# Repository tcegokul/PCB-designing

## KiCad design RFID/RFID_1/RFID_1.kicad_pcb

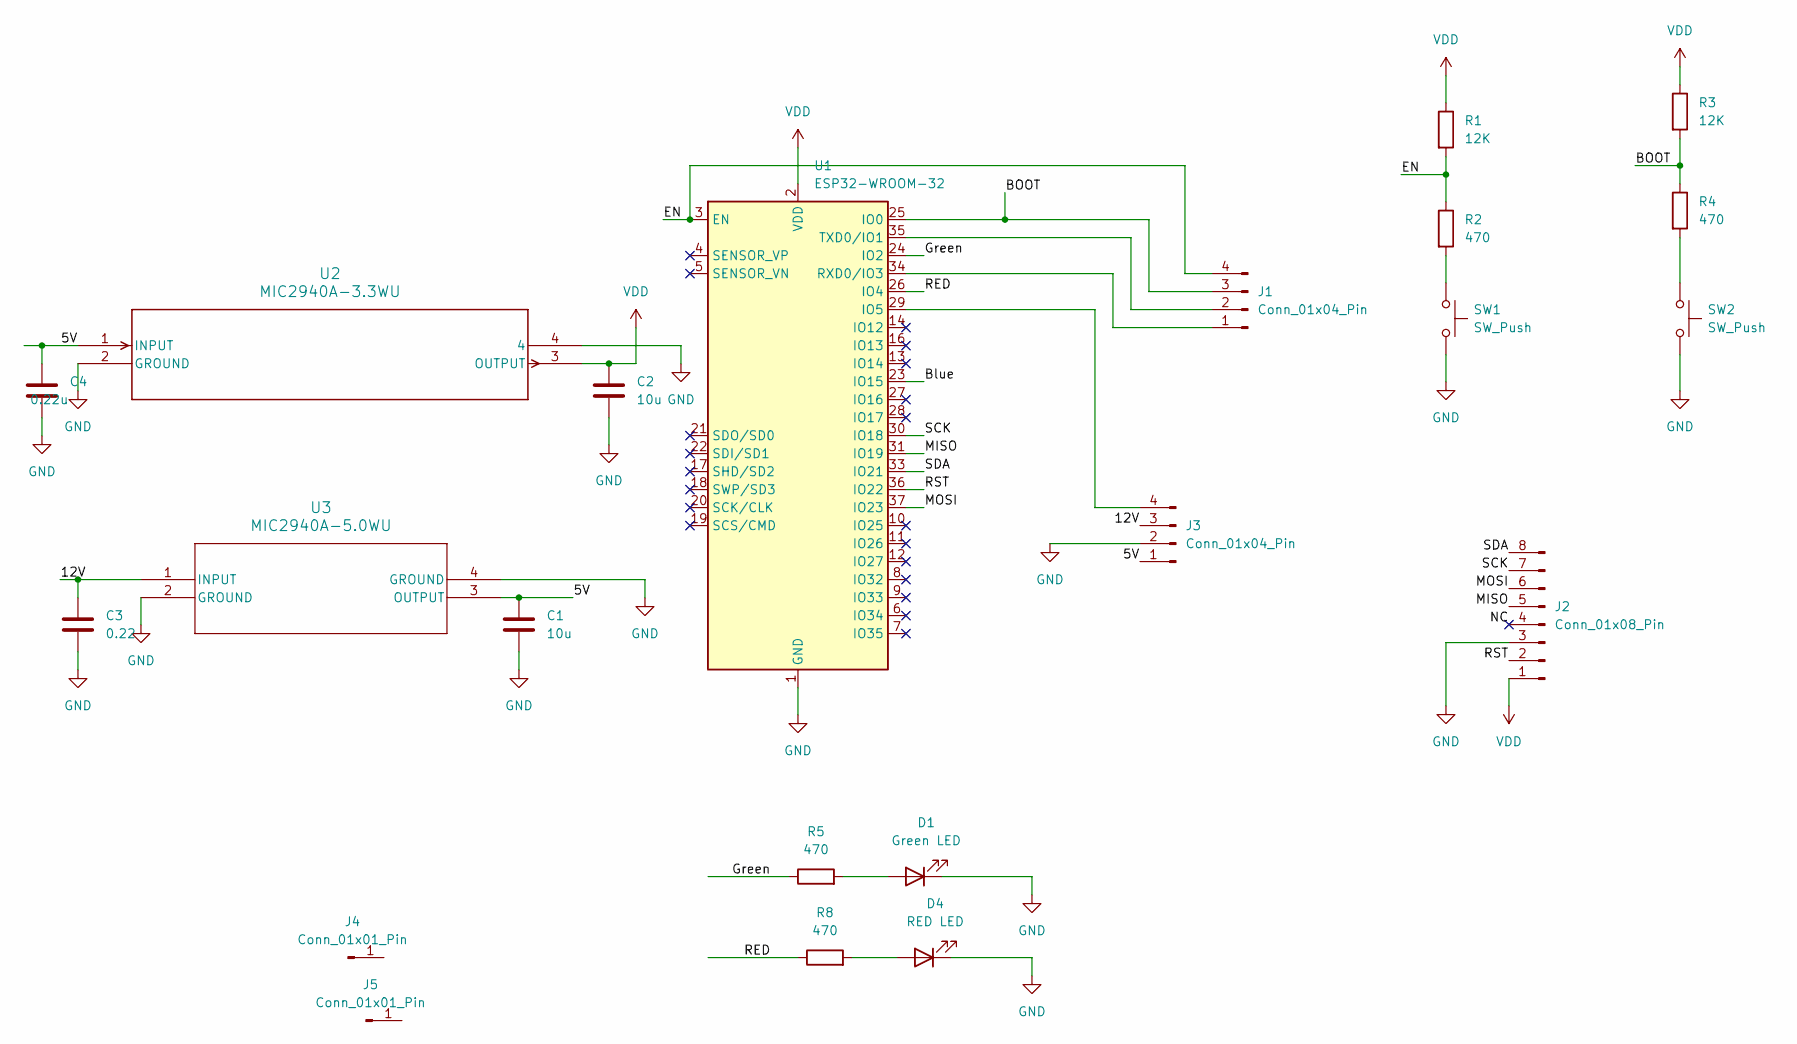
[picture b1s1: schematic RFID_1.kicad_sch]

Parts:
C1, C2: 10u; C_0805_2012Metric_Pad1.18x1.45mm_HandSolder
C3: 0.22; C_0805_2012Metric_Pad1.18x1.45mm_HandSolder
C4: 0.22u; C_0805_2012Metric_Pad1.18x1.45mm_HandSolder
D1: Green LED; LED_0805_2012Metric_Pad1.15x1.40mm_HandSolder
D4: RED LED; LED_0805_2012Metric_Pad1.15x1.40mm_HandSolder
J1: Conn_01x04_Pin; PinHeader_1x04_P2.54mm_Vertical
J2: Conn_01x08_Pin; PinSocket_1x08_P2.54mm_Vertical
J3: Conn_01x04_Pin; CONN4_500000G_AMP
J4, J5: Conn_01x01_Pin; pad_clearancefu
R1, R3: 12K; R_0805_2012Metric_Pad1.20x1.40mm_HandSolder
R2, R4, R5, R8: 470; R_0805_2012Metric_Pad1.20x1.40mm_HandSolder
SW1, SW2: SW_Push; SW_Push_1P1T_NO_6x6mm_H9.5mm
U1: ESP32-WROOM-32
U2: MIC2940A-3.3WU; TO263-3LD_MCH
U3: MIC2940A-5.0WU; TO263-3LD_MCH

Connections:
/5V: C1.1, C4.1, J3.1, U2.1 (INPUT), U3.3 (OUTPUT)
/12V: C3.1, J3.3, U3.1 (INPUT)
/BOOT: J1.3, R3.2, R4.1, U1.25 (IO0)
/Blue: U1.23 (IO15)
/EN: J1.4, R1.2, R2.1, U1.3 (EN)
/Green: R5.1, U1.24 (IO2)
/MISO: J2.5, U1.31 (IO19)
/MOSI: J2.6, U1.37 (IO23)
/NC: J2.4
/RED: R8.1, U1.26 (IO4)
/RST: J2.2, U1.36 (IO22)
/SCK: J2.7, U1.30 (IO18)
/SDA: J2.8, U1.33 (IO21)
GND: C1.2, C2.2, C3.2, C4.2, D1.1 (K), D4.1 (K), J2.3, J3.2, J4.1, J5.1, SW1.2, SW2.2, U1.1 (GND), U1.15 (GND), U1.38 (GND), U1.39 (GND), U2.2 (GROUND), U2.4, U3.2 (GROUND), U3.4 (GROUND)
unnamed: D1.2 (A), R5.2
unnamed: D4.2 (A), R8.2
unnamed: J1.1, U1.34 (RXD0/IO3)
unnamed: J1.2, U1.35 (TXD0/IO1)
unnamed: J3.4, U1.29 (IO5)
unnamed: R2.2, SW1.1
unnamed: R4.2, SW2.1
VDD: C2.1, J2.1, R1.1, R3.1, U1.2 (VDD), U2.3 (OUTPUT)

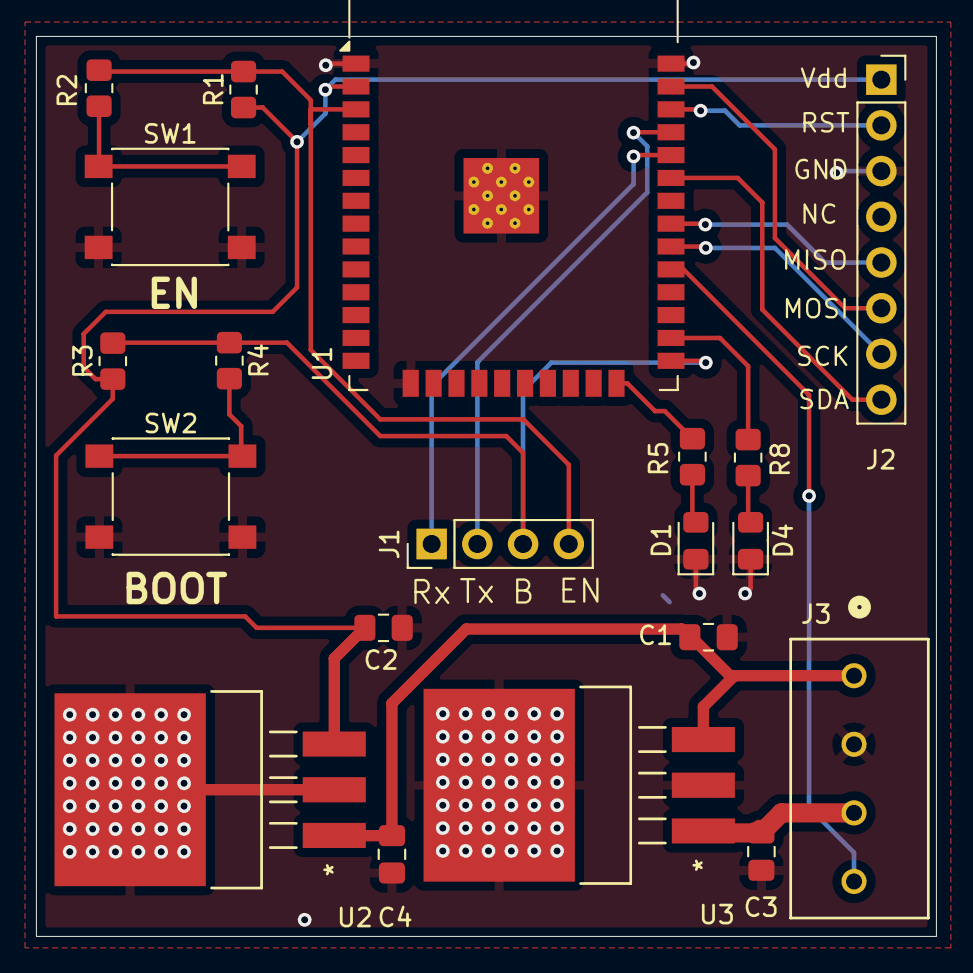
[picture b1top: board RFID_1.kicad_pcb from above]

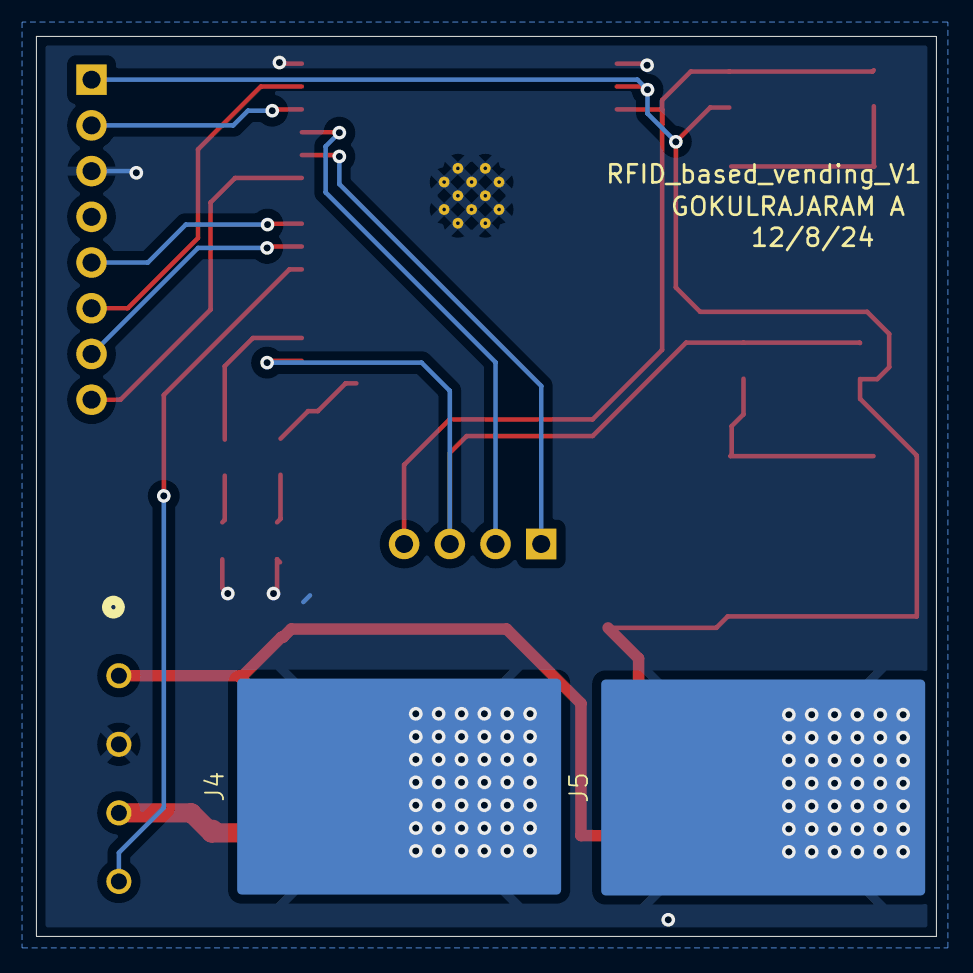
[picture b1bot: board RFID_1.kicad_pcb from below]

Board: 2 copper layers, 50.0 x 50.0 mm, 22 parts (2 on the bottom side), 20 nets.

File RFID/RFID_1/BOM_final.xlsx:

Sr No | Qunatity | Reference | Value | Part type | PCB foot print | Manufacture part number / Generic part number | Manufacturer Name | Description
1 | 2 | C1,C2 | 10uF | CAP | Capacitor_SMD:C_0805_2012Metric_Pad1.18x1.45mm_HandSolder | GPC0805106-16
2 | 1 | C3,C4 | 0.22uF | CAP | Capacitor_SMD:C_0805_2012Metric_Pad1.18x1.45mm_HandSolder | CL21B224KCFSNWE | Samsung Electro-Me chanics
3 | 1 | D1 | Green LED | LED | LED_SMD:LED_0805_2012Metric_Pad1.15x1.40mm_HandSolder | 150080BS75000 | Würth Elektronik | blue lEDs
4 | 1 | D4 | RED LED | LED | LED_SMD:LED_0805_2012Metric_Pad1.15x1.40mm_HandSolder | 150080BS75000 | Würth Elektronik | Blue LEDs
5 | 1 | J1 | Conn_01x04_Pin | male Connector | Connector_PinHeader_2.54mm:PinHeader_1x04_P2.54mm_Vertical | PH1-04-UA
6 | 1 | J3 | Conn_01x04_Pin | wire to board connector | footprints_screw_connector:CONN4_500000G_AMP | YO0421500000G | Amphenol Anytek | 4 Position Wire to Board Terminal Block Horizontal with Board 0.150" (3.81mm) T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
7 | 1 | J2 | Conn_01x08_Pin | Female connector | Connector_PinSocket_2.54mm:PinSocket_1x08_P2.54mm_Vertical | 61300811821
8 | 2 | R1,R3 | 12k | Resistor | Resistor_SMD:R_0805_2012Metric_Pad1.20x1.40mm_HandSolder | RMCF0805JT12K0 | Stackpole Electronics Inc | RES 12K OHM 5% 1/8W 0805
9 | 4 | R2,R4,R5,R8 | 470 | Resistor | Resistor_SMD:R_0805_2012Metric_Pad1.20x1.40mm_HandSolder | GPR0805470R
10 | 1 | U1 | ESP32-Wroom-32 | ESP32-WROOM-32-N4 | RF_Module:ESP32-WROOM-32 | ESP32-WROOM-32E-N4 | Espressif Systems | RF TXRX MOD BT WIFI TH SMD
11 | 1 | U2 | MIC2940A-3.3WU | MIC2940A-3.3WU | footprints:TO263-3LD_MCH | MIC2940A-3.3WU | Microchip Technology | IC REG LINEAR 3.3V 1.25A TO263-3
12 | 1 | U3 | MIC2940A-5.0WU | MIC2940A-5.0WU | footprints_5v:TO263-3LD_MCH | MIC2940A-5.0WU | Microchip Technology | IC REG LINEAR 5V 1.25A TO263-3
13 | 2 | SW1,SW2 | Switch | Switch | Button_Switch_SMD:SW_Push_1P1T_NO_6x6mm_H9.5mm | FSM2JSMAATR | TE Connectivity ALCOSWITCH Switches | SWITCH TACTILE SPST-NO 0.05A 24V

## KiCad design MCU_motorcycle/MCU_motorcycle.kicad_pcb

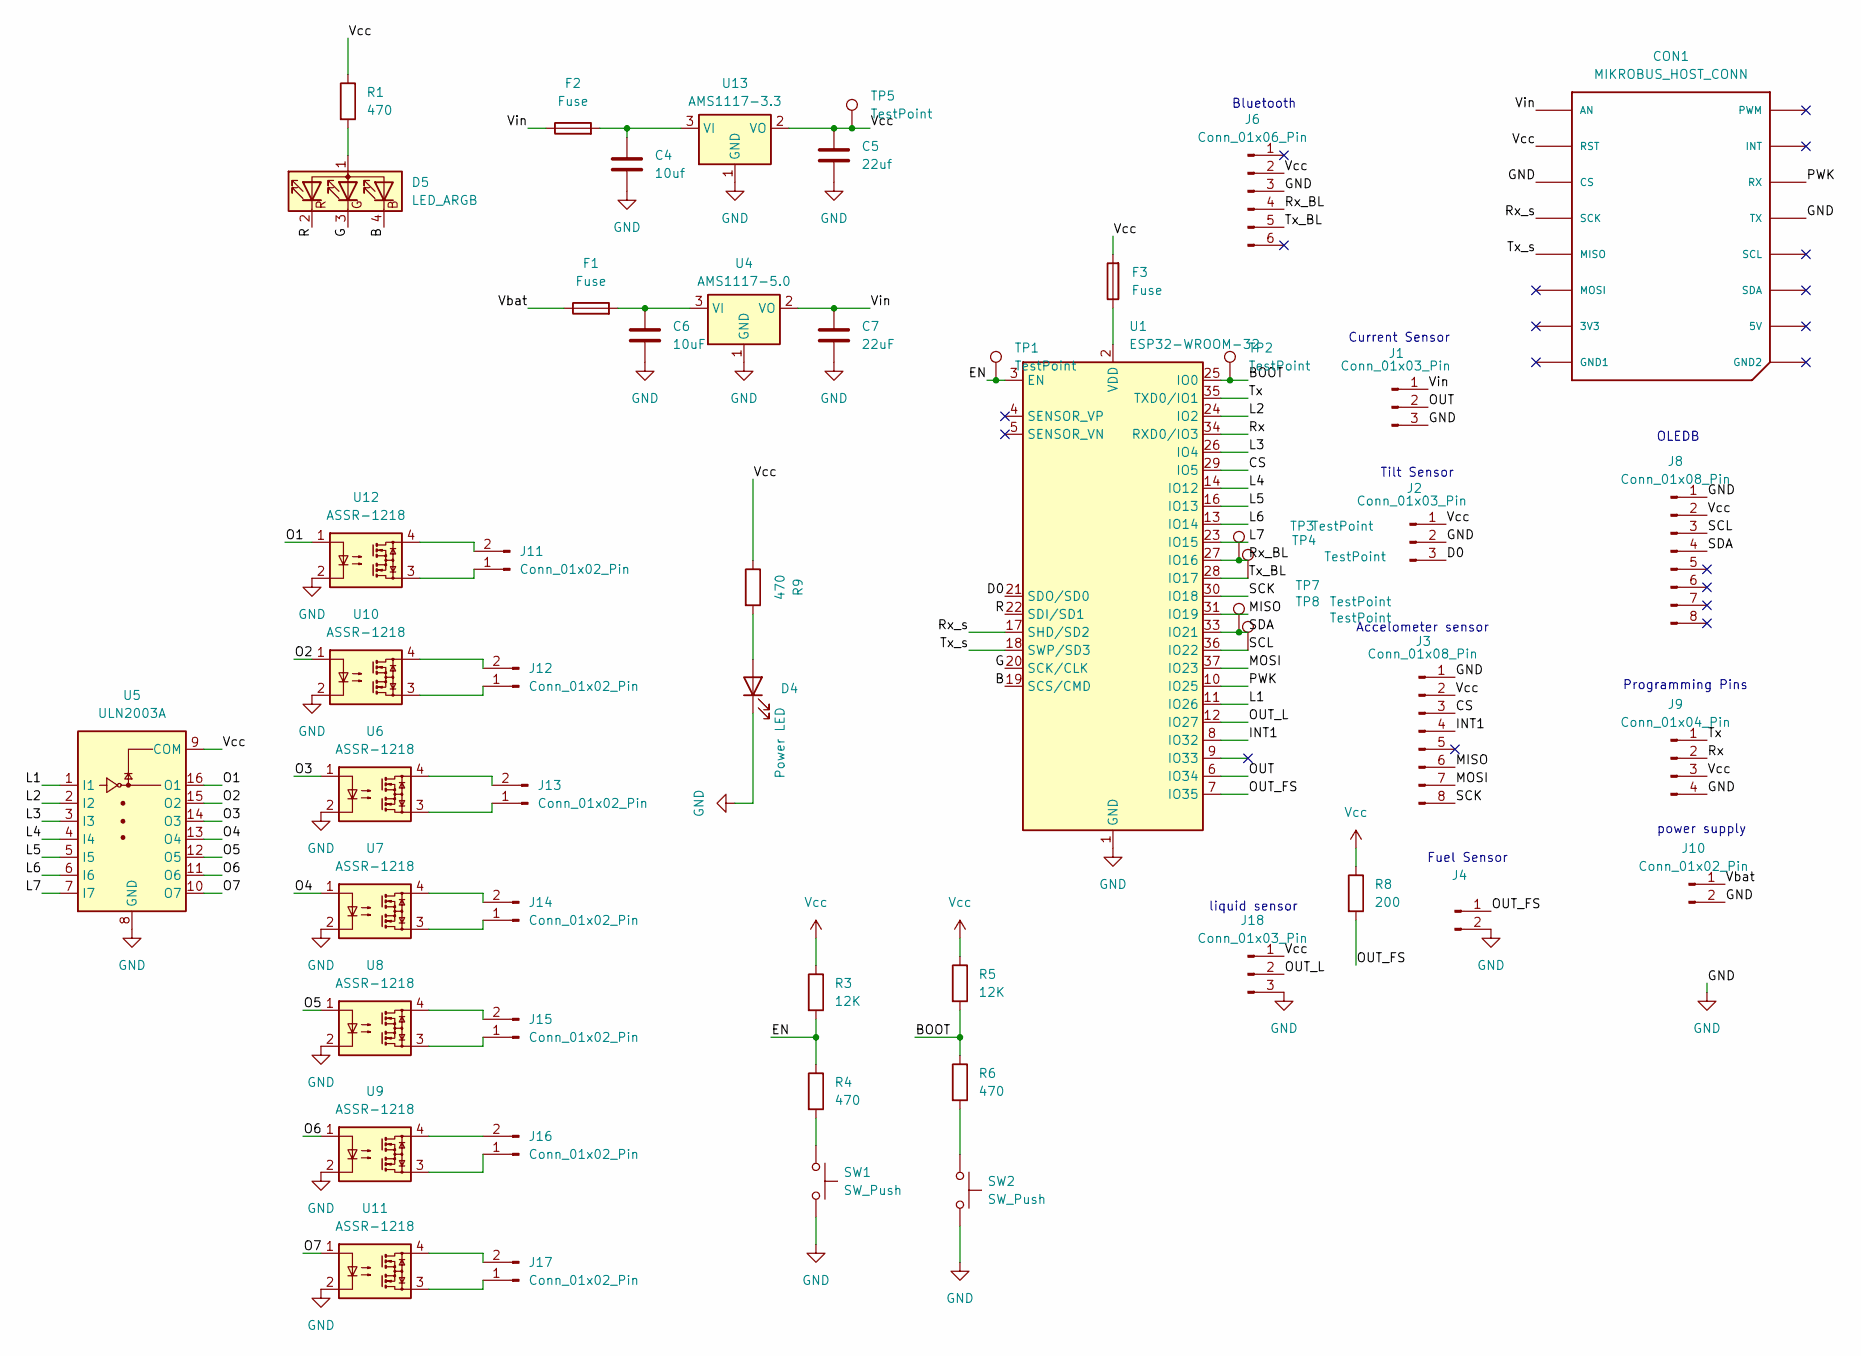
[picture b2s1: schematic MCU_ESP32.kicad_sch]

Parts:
C4: 10uf; C_0603_1608Metric_Pad1.08x0.95mm_HandSolder
C5: 22uf; C_0603_1608Metric_Pad1.08x0.95mm_HandSolder
C6: 10uF; C_0603_1608Metric_Pad1.08x0.95mm_HandSolder
C7: 22uF; C_0603_1608Metric_Pad1.08x0.95mm_HandSolder
CON1: MIKROBUS_HOST_CONN
D4: Power LED; LED_0603_1608Metric_Pad1.05x0.95mm_HandSolder
D5: LED_ARGB; LED_AAA3528LSEKJ3ZGKQBKS
F1, F2, F3: Fuse; Fuse_1206_3216Metric_Pad1.42x1.75mm_HandSolder
J1, J18: Conn_01x03_Pin; PinSocket_1x03_P2.54mm_Vertical
J2: Conn_01x03_Pin; PinSocket_1x03_P2.54mm_Horizontal
J3, J8: Conn_01x08_Pin; PinSocket_1x08_P2.54mm_Vertical
J4: Conn_01x02_Pin; PinSocket_1x02_P2.54mm_Vertical
J6: Conn_01x06_Pin; PinSocket_1x06_P2.54mm_Horizontal
J9: Conn_01x04_Pin; PinSocket_1x04_P2.54mm_Vertical
J10, J11, J12, J13, J14, J15, J16, J17: Conn_01x02_Pin; TE_282837-2
R1, R4, R6, R9: 470; R_0805_2012Metric_Pad1.20x1.40mm_HandSolder
R3, R5: 12K; R_0805_2012Metric_Pad1.20x1.40mm_HandSolder
R8: 200; R_0805_2012Metric_Pad1.20x1.40mm_HandSolder
SW1, SW2: SW_Push; SW_Push_1P1T_NO_6x6mm_H9.5mm
TP1, TP2, TP3, TP4, TP5, TP7, TP8: TestPoint; TestPoint_Pad_1.5x1.5mm
U1: ESP32-WROOM-32
U4: AMS1117-5.0; SOT-223-3_TabPin2
U5: ULN2003A; DIP762W46P254L1969H533Q16
U6, U7, U8, U9, U10, U11, U12: ASSR-1218; SIP-4_DMO
U13: AMS1117-3.3; SOT-223-3_TabPin2

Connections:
/MCU_ESP32/B: D5.4 (BK), U1.19 (SCS/CMD)
/MCU_ESP32/BOOT: R5.2, R6.1, TP2.1, U1.25 (IO0)
/MCU_ESP32/CS: J3.3, U1.29 (IO5)
/MCU_ESP32/D0: J2.3, U1.21 (SDO/SD0)
/MCU_ESP32/EN: R3.2, R4.1, TP1.1, U1.3 (EN)
/MCU_ESP32/G: D5.3 (GK), U1.20 (SCK/CLK)
/MCU_ESP32/INT1: J3.4, U1.8 (IO32)
/MCU_ESP32/L1: U1.11 (IO26), U5.1 (I1)
/MCU_ESP32/L2: U1.24 (IO2), U5.2 (I2)
/MCU_ESP32/L3: U1.26 (IO4), U5.3 (I3)
/MCU_ESP32/L4: U1.14 (IO12), U5.4 (I4)
/MCU_ESP32/L5: U1.16 (IO13), U5.5 (I5)
/MCU_ESP32/L6: U1.13 (IO14), U5.6 (I6)
/MCU_ESP32/L7: U1.23 (IO15), U5.7 (I7)
/MCU_ESP32/MISO: J3.6, U1.31 (IO19)
/MCU_ESP32/MOSI: J3.7, U1.37 (IO23)
/MCU_ESP32/O1: U5.16 (O1), U12.1
/MCU_ESP32/O2: U5.15 (O2), U10.1
/MCU_ESP32/O3: U5.14 (O3), U6.1
/MCU_ESP32/O4: U5.13 (O4), U7.1
/MCU_ESP32/O5: U5.12 (O5), U8.1
/MCU_ESP32/O6: U5.11 (O6), U9.1
/MCU_ESP32/O7: U5.10 (O7), U11.1
/MCU_ESP32/OUT: J1.2, U1.6 (IO34)
/MCU_ESP32/OUT_FS: J4.1, R8.2, U1.7 (IO35)
/MCU_ESP32/OUT_L: J18.2, U1.12 (IO27)
/MCU_ESP32/PWK: CON1.P14 (RX), U1.10 (IO25)
/MCU_ESP32/R: D5.2 (RK), U1.22 (SDI/SD1)
/MCU_ESP32/Rx: J9.2, U1.34 (RXD0/IO3)
/MCU_ESP32/Rx_BL: J6.4, TP3.1, U1.27 (IO16)
/MCU_ESP32/Rx_s: CON1.P4 (SCK), U1.17 (SHD/SD2)
/MCU_ESP32/SCK: J3.8, U1.30 (IO18)
/MCU_ESP32/SCL: J8.3, TP8.1, U1.36 (IO22)
/MCU_ESP32/SDA: J8.4, TP7.1, U1.33 (IO21)
/MCU_ESP32/Tx: J9.1, U1.35 (TXD0/IO1)
/MCU_ESP32/Tx_BL: J6.5, TP4.1, U1.28 (IO17)
/MCU_ESP32/Tx_s: CON1.P5 (MISO), U1.18 (SWP/SD3)
/MCU_ESP32/Vbat: F1.1, J10.1
/MCU_ESP32/Vin: C7.1, CON1.P1 (AN), F2.1, J1.1, U4.2 (VO)
GND: C4.2, C5.2, C6.2, C7.2, CON1.P3 (CS), CON1.P13 (TX), D4.1 (K), J1.3, J2.2, J3.1, J4.2, J6.3, J8.1, J9.4, J10.2, J18.3, SW1.2, SW2.2, U1.1 (GND), U1.15 (GND), U1.38 (GND), U1.39 (GND), U4.1 (GND), U5.8 (GND), U6.2, U7.2, U8.2, U9.2, U10.2, U11.2, U12.2, U13.1 (GND)
unnamed: D4.2 (A), R9.2
unnamed: D5.1 (A), R1.2
unnamed: J11.1, U12.3
unnamed: J11.2, U12.4
unnamed: J12.1, U10.3
unnamed: J12.2, U10.4
unnamed: J13.1, U6.3
unnamed: J13.2, U6.4
unnamed: J14.1, U7.3
unnamed: J14.2, U7.4
unnamed: J15.1, U8.3
unnamed: J15.2, U8.4
unnamed: J16.1, U9.3
unnamed: J16.2, U9.4
unnamed: J17.1, U11.3
unnamed: J17.2, U11.4
unnamed: R4.2, SW1.1
unnamed: R6.2, SW2.1
unnamed: F3.1, U1.2 (VDD)
unnamed: C6.1, F1.2, U4.3 (VI)
unnamed: C4.1, F2.2, U13.3 (VI)
Vcc: C5.1, CON1.P2 (RST), F3.2, J2.1, J3.2, J6.2, J8.2, J9.3, J18.1, R1.1, R3.1, R5.1, R8.1, R9.1, TP5.1, U5.9 (COM), U13.2 (VO)

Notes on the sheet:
Bluetooth
Tilt Sensor
Current Sensor
liquid sensor
Accelometer sensor
power supply
Fuel Sensor
Programming Pins
OLEDB

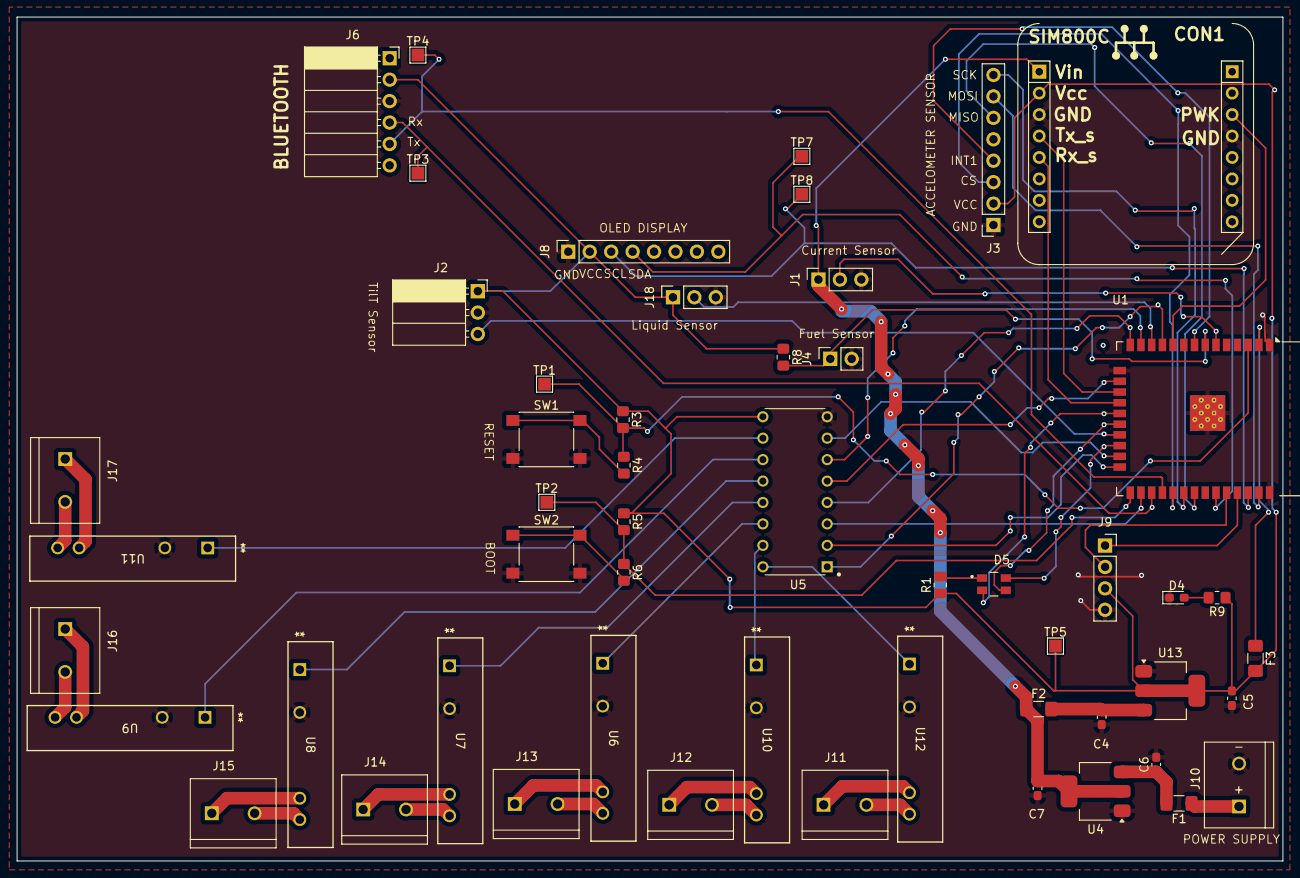
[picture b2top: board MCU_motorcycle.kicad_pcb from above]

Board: 2 copper layers, 150.0 x 100.0 mm, 53 parts (0 on the bottom side), 62 nets.
